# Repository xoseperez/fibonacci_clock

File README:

# Fibonacci Clock

Some months ago Philippe Chrétien opened a Kickstarter with his [Fibonacci Clock][1].
I immediately fell in love with it. It was awesome, mathematical, colorful and
open source. A truly makers project. At 100€ the unit it was too expensive
for me but he gathered almost 128k€. He shipped the last of the 1242 clocks
just a few weeks ago. And I got mine more or less in the same dates, but of
course, I did it myself.

You can check how he did it in his [instructables page][2], or browse this repository
with my designs and code.

## Hardware

### The clock

The hardware has been designed using [OpenSCad][2]. It's basically a box with compartments
inside another box. Originally I planned to use 8-10mm thick wood for the outside
box but finally I've used the same DMF as in the inner box. Inside the box there is
a custom PCB wth an RTC and nine 12mm RGB LEDs with WS2812B drivers.

### The controller

The controller is a custom PCB designed to serve different purposes. On one hand
there is an RTC and a uC (ATMega328P, same as an Arduino UNO). The user interface
are 4 big 12x12mm buttons and, optionally there is an SD card reader (more about
this in a future project).

It can be powered with 5V via a 2.1x5.5mm barrel plug or a screw terminal, there is
an FTDI-compatible header to program it and a 3-wire screw terminal to connect
Neopixel-like strips.

Please check the .sch and .brd files for Eagle in the schema folder.

## Firmware

The project is ready to be build using [PlatformIO][4].
Please refer to their web page for instructions on how to install the builder.
Once installed:

```bash
> cd code
> platformio init -b uno
> platformio run
> platformio run --target upload
```

Library dependencies are automatically managed via PlatformIO Library Manager.

[1]: https://www.kickstarter.com/projects/basbrun/fibonacci-clock-an-open-source-clock-for-nerds-wit
[2]: http://www.instructables.com/id/The-Fibonacci-Clock/
[3]: http://www.openscad.org
[4]: http://www.platformio.org

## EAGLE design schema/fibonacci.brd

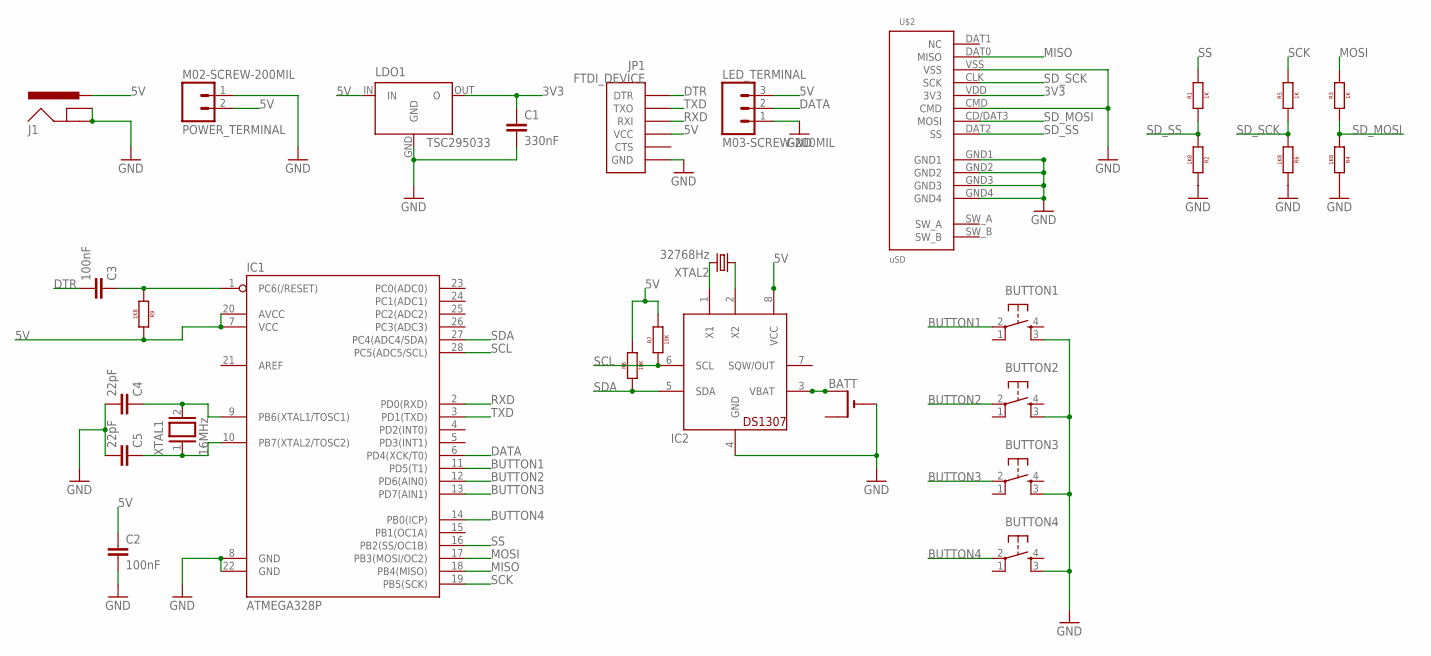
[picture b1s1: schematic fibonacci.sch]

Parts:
BATT: CR2032SMT; CR2032-SMD
BUTTON1: B1; TACTILE_BUTTON
BUTTON2: B2; TACTILE_BUTTON
BUTTON3: B3; TACTILE_BUTTON
BUTTON4: B4; TACTILE_BUTTON
C1: 330nF; C050-025X075
C2, C3: 100nF; C050-025X075
C4, C5: 22pF; C050-025X075
IC1: ATMEGA328P; DIL28-3
IC2: DS1307; DIL08
J1: POWER_JACKPTH; POWER_JACK_PTH
JP1: FTDI_DEVICE; FTDI_DEVICE_SIDE
LDO1: TSC295033; TO92
LED_TERMINAL: M03-SCREW-200MIL; SCREWTERMINAL-200MIL-3
POWER_TERMINAL: M02-SCREW-200MIL; SCREWTERMINAL-200MIL-2
R1, R3, R5: 1K; AXIAL-0.4
R2, R4, R6, R9: 1K8; AXIAL-0.4
R7, R8: 10K; AXIAL-0.4
U$2: uSD; DM3D
XTAL1: 16MHz; QS
XTAL2: 32768Hz; TC38H

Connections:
3V3: C1.1, LDO1.OUT (O), U$2.VDD (3V3)
5V: C2.1, IC1.7 (VCC), IC1.20 (AVCC), IC2.8 (VCC), J1.PWR, JP1.P$4 (VCC), LDO1.IN, LED_TERMINAL.3, POWER_TERMINAL.2, R7.P$2 (2), R8.P$2 (2), R9.P$2 (2)
BUTTON1: BUTTON1.2 (SWA1), IC1.11 (PD5(T1))
BUTTON2: BUTTON2.2 (SWA1), IC1.12 (PD6(AIN0))
BUTTON3: BUTTON3.2 (SWA1), IC1.13 (PD7(AIN1))
BUTTON4: BUTTON4.2 (SWA1), IC1.14 (PB0(ICP))
DATA: IC1.6 (PD4(XCK/T0)), LED_TERMINAL.2
DTR: C3.2, JP1.P$1 (DTR)
GND: BATT.-, BUTTON1.3 (SWB2), BUTTON2.3 (SWB2), BUTTON3.3 (SWB2), BUTTON4.3 (SWB2), C1.2, C2.2, C4.2, C5.2, IC1.8 (GND), IC1.22 (GND), IC2.4 (GND), J1.GND, J1.GNDBREAK, JP1.P$6 (GND), LDO1.GND, LED_TERMINAL.1, POWER_TERMINAL.1, R2.P$2 (2), R4.P$2 (2), R6.P$2 (2), U$2.CMD, U$2.GND1, U$2.GND2, U$2.GND3, U$2.GND4, U$2.VSS
MISO: IC1.18 (PB4(MISO)), U$2.DAT0 (MISO)
MOSI: IC1.17 (PB3(MOSI/OC2)), R3.P$2 (2)
unnamed: C3.1, IC1.1 (PC6(/RESET)), R9.P$1 (1)
unnamed: C4.1, IC1.9 (PB6(XTAL1/TOSC1)), XTAL1.2
unnamed: C5.1, IC1.10 (PB7(XTAL2/TOSC2)), XTAL1.1
unnamed: BATT.+$1 (+), IC2.3 (VBAT)
unnamed: IC2.1 (X1), XTAL2.2
unnamed: IC2.2 (X2), XTAL2.1
RXD: IC1.2 (PD0(RXD)), JP1.P$3 (RXI)
SCK: IC1.19 (PB5(SCK)), R5.P$2 (2)
SCL: IC1.28 (PC5(ADC5/SCL)), IC2.6 (SCL), R7.P$1 (1)
SDA: IC1.27 (PC4(ADC4/SDA)), IC2.5 (SDA), R8.P$1 (1)
SD_MOSI: R3.P$1 (1), R4.P$1 (1), U$2.CD/DAT3 (MOSI)
SD_SCK: R5.P$1 (1), R6.P$1 (1), U$2.CLK (SCK)
SD_SS: R1.P$1 (1), R2.P$1 (1), U$2.DAT2 (SS)
SS: IC1.16 (PB2(SS/OC1B)), R1.P$2 (2)
TXD: IC1.3 (PD1(TXD)), JP1.P$2 (TXO)

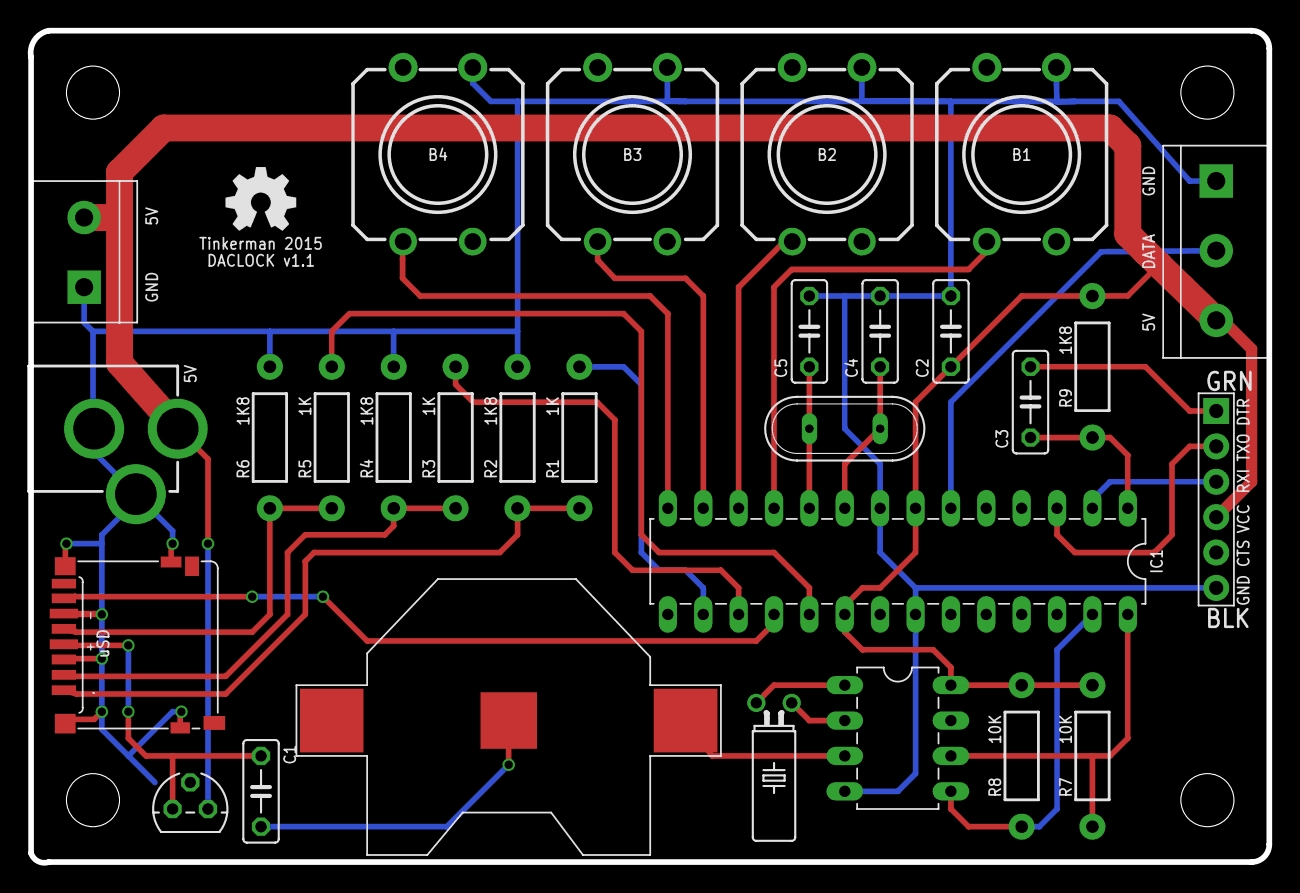
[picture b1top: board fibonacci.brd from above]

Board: 2 copper layers, 88.9 x 59.7 mm, 29 parts (0 on the bottom side), 26 nets.

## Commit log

2015-05-21 SCAD models
2015-06-11 Beta revision of box model
2015-06-13 Fist version of schema and board layout
2015-06-13 Improved laser cutter models
2015-06-18 Board schema and layout v0.9
2015-06-18 Added beefier terminals to board
2015-06-25 Final PCB version and gerbers
2015-10-30 Working code version 0.1
2015-10-30 Schema and board layout, datasheets
2015-10-30 Box models
2015-10-30 Children-proof time changing, but easier to read. Pause rainbow cycle
2015-10-30 Fix bug when overflowing minutes
2015-11-06 Added black palettes and some code changes
2015-11-06 Migrated to platformio code builder
2015-11-06 Version 1.2 of the layout sent to fab
2015-11-09 Reset seconds after changing time to sync clock
2015-11-09 Using platformio as library manager
2015-11-10 README file
2015-12-16 Changed RTC lib to Adafruit's fork of JeeLab's library for Arduino
2017-04-26 Update repo
2018-10-12 Update serial mnitor speed to 115200
2021-05-07 Add .gitignore

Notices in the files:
parts and their libraries:
SparkFun-Connectors: Licensing: CC v3.0 Share-Alike You are welcome to use this library for commercial purposes.
SparkFun-Aesthetics: Licensing: Creative Commons ShareAlike 4.0 International - https://creativecommons.org/licenses/by-sa/4.0
